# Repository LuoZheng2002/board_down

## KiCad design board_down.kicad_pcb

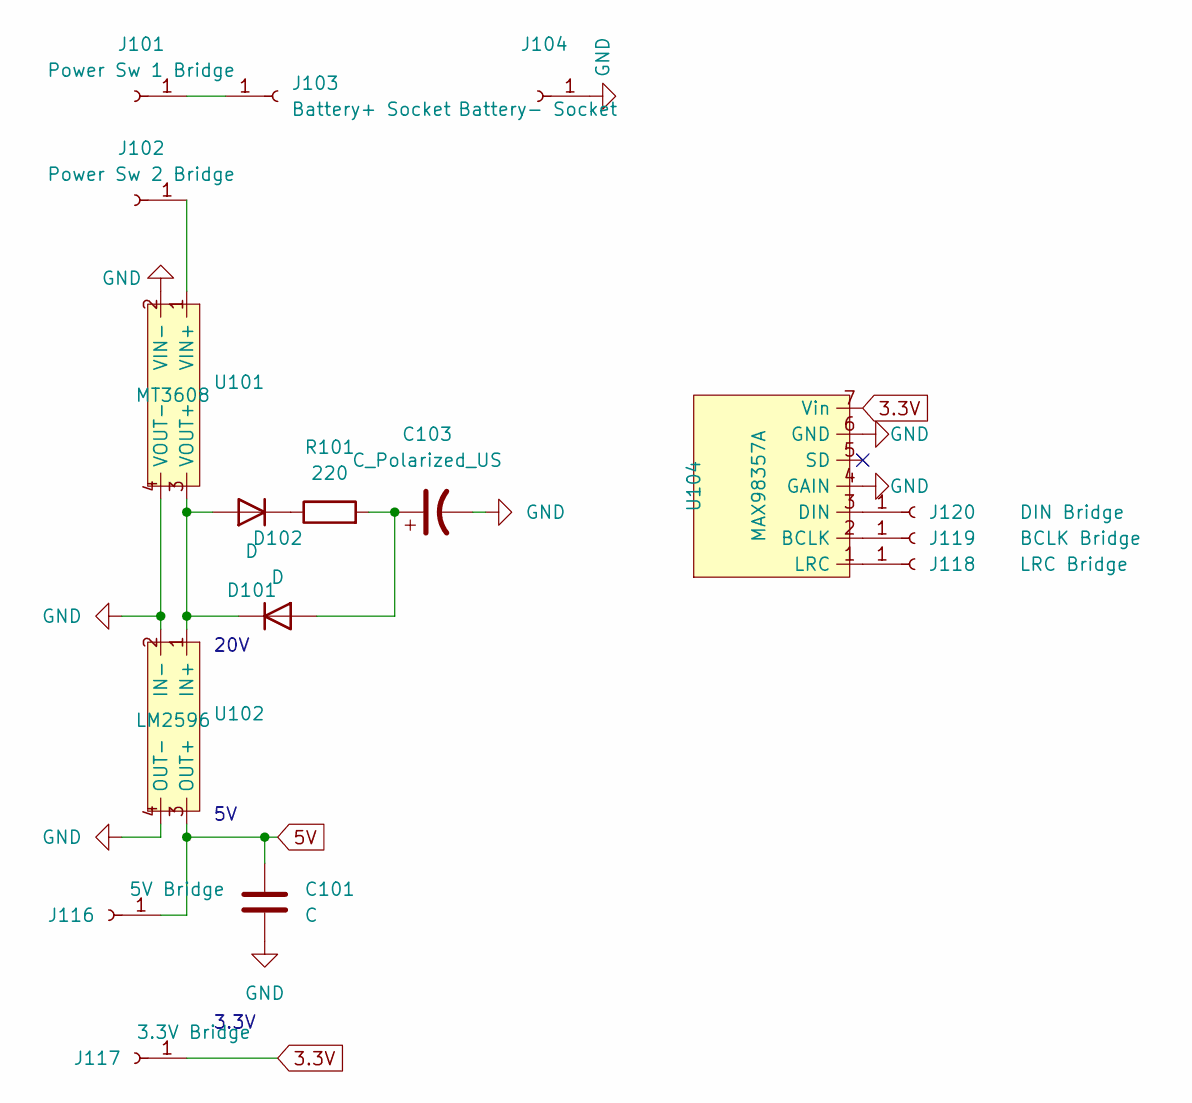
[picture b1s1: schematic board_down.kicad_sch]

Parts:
C101: C; CP_Radial_D5.0mm_P2.50mm
C103: C_Polarized_US; CP_Radial_D18.0mm_P7.50mm
D101, D102: D; D_DO-34_SOD68_P7.62mm_Horizontal
J101: Power Sw 1 Bridge; PinSocket_1x01_P2.54mm_Vertical
J102: Power Sw 2 Bridge; PinSocket_1x01_P2.54mm_Vertical
J103: Battery+ Socket; PinSocket_1x01_P2.54mm_Vertical
J104: Battery- Socket; PinSocket_1x01_P2.54mm_Vertical
J116: 5V Bridge; PinSocket_1x01_P2.54mm_Vertical
J117: 3.3V Bridge; PinSocket_1x01_P2.54mm_Vertical
J118: LRC Bridge; PinSocket_1x01_P2.54mm_Vertical
J119: BCLK Bridge; PinSocket_1x01_P2.54mm_Vertical
J120: DIN Bridge; PinSocket_1x01_P2.54mm_Vertical
R101: 220; R_Axial_DIN0207_L6.3mm_D2.5mm_P7.62mm_Horizontal
U101: MT3608
U102: LM2596
U104: MAX98357A

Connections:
3.3V: J117.1, U104.7 (Vin)
5V: C101.1, J116.1, U102.3 (OUT+)
GND: C101.2, C103.2, J104.1, U101.2 (VIN-), U101.4 (VOUT-), U102.2 (IN-), U102.4 (OUT-), U104.4 (GAIN), U104.6 (GND)
unnamed: D101.2 (A), D102.1 (K), U101.3 (VOUT+), U102.1 (IN+)
unnamed: D101.1 (K), R101.1
unnamed: C103.1, D102.2 (A), R101.2
unnamed: J101.1, J103.1
unnamed: J102.1, U101.1 (VIN+)
unnamed: J118.1, U104.1 (LRC)
unnamed: J119.1, U104.2 (BCLK)
unnamed: J120.1, U104.3 (DIN)

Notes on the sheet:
3.3V
20V

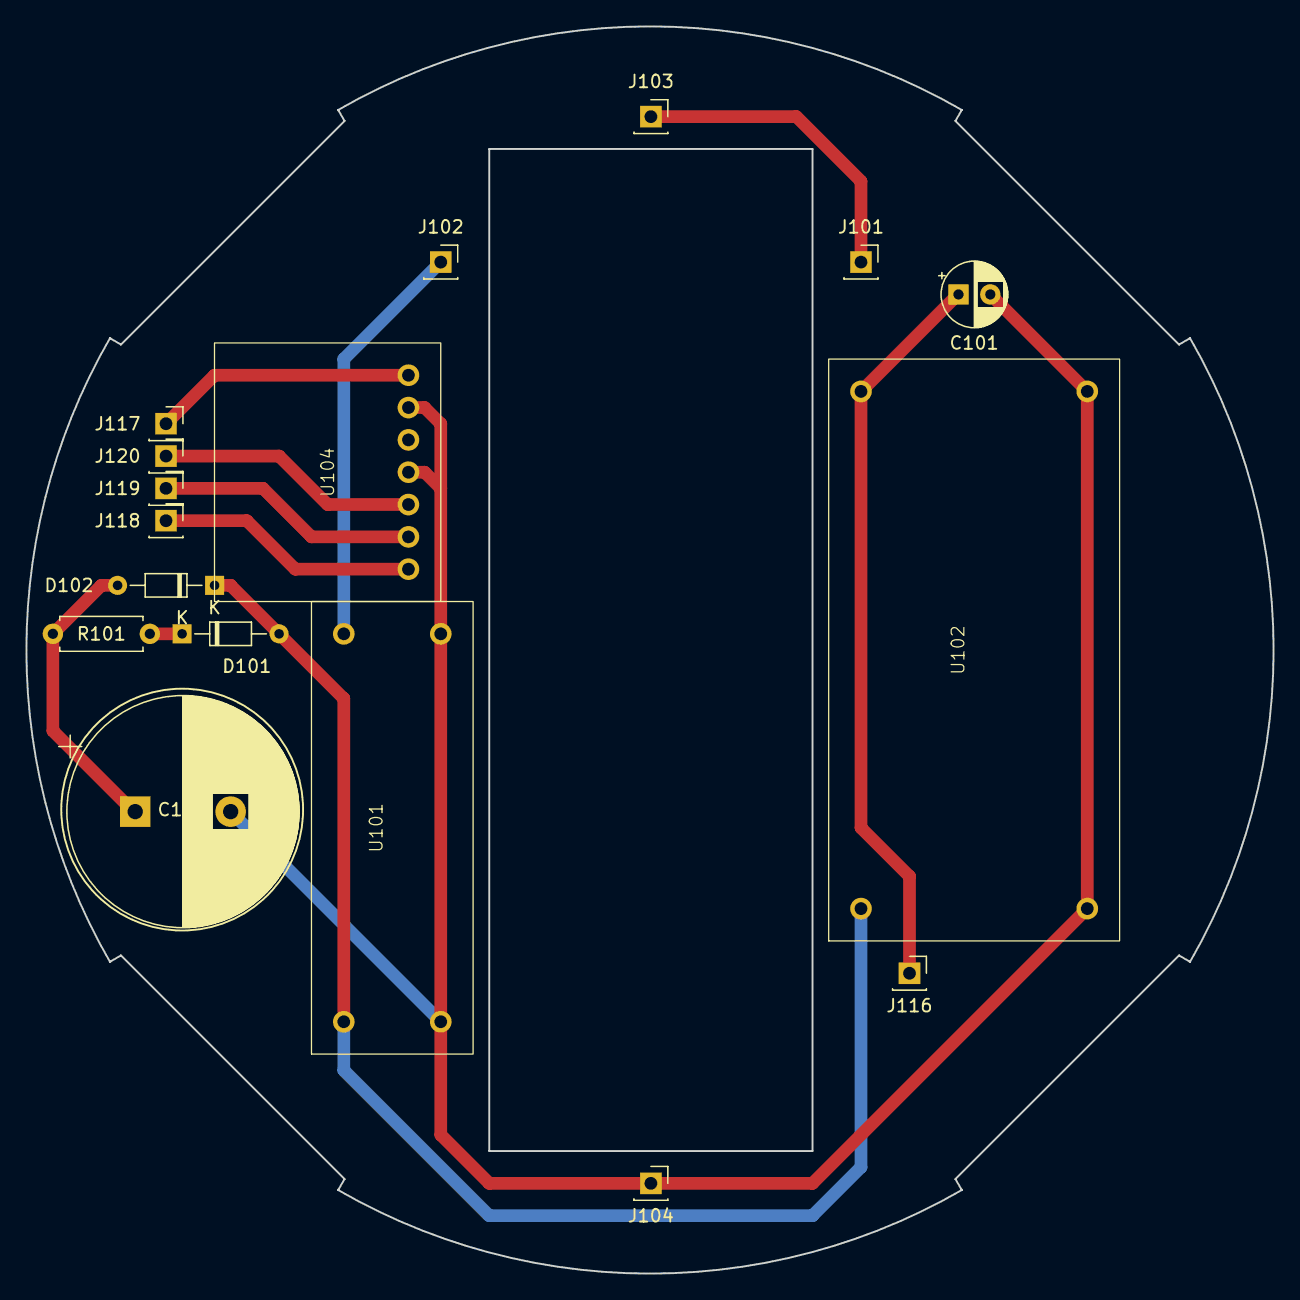
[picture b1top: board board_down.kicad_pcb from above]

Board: 2 copper layers, 98.0 x 98.0 mm, 17 parts (0 on the bottom side), 11 nets.

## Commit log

2024-02-07 checkpoint
2024-02-07 changed_rectangle
